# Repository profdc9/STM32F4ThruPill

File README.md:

This is a Bluepill pinout-compatible devboard for the STM32F405RGT6 LQFP-64 microcontroller.
It uses all through-hole parts except for the microcontroller
and is intended to be an alternative that is easier to assemble
should the Bluepill not be available or suitable.  
This material is copyrighted by Daniel Marks (KW4TI) and licensed under
the Creative Commons License CC-BY-SA 4.0.  Software is copyrighted using the zlib
open-source license.

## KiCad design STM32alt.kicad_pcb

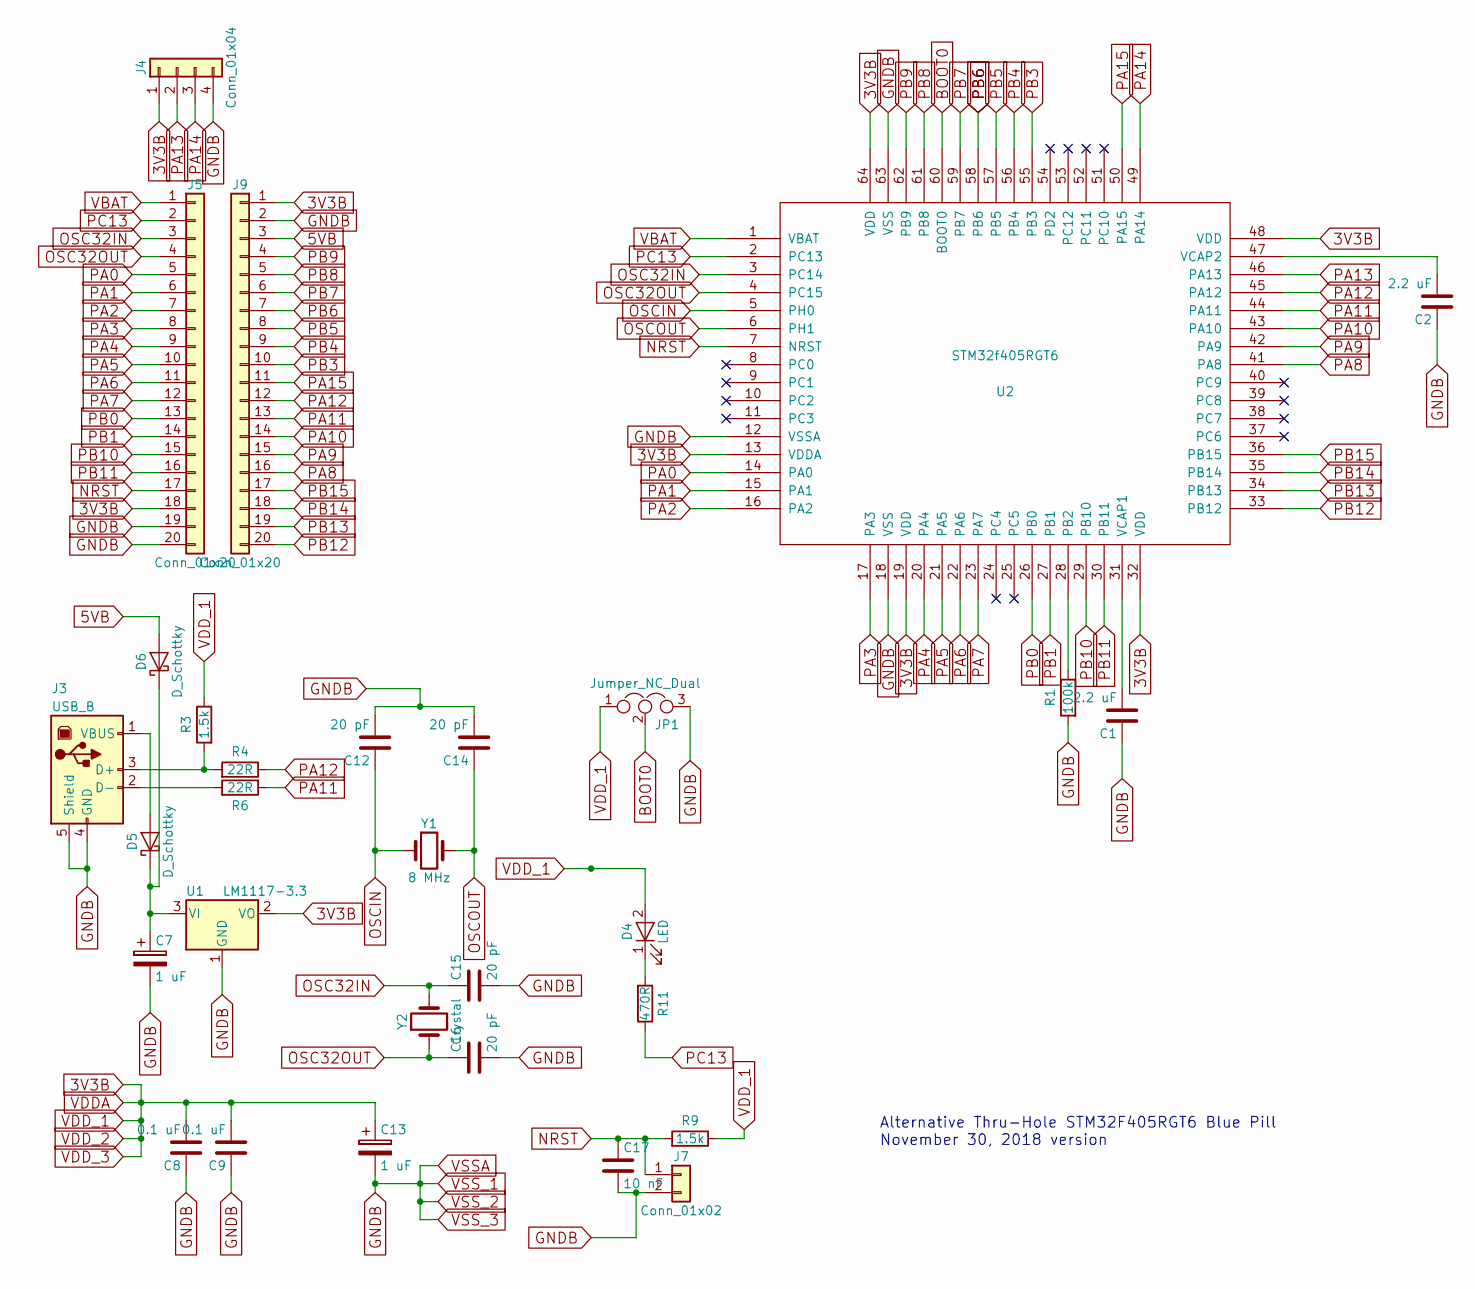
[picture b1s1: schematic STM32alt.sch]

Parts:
C1, C2: 2.2 uF; C_Disc_D5.0mm_W2.5mm_P2.50mm
C7, C13: 1 uF; CP_Radial_D5.0mm_P2.50mm
C8, C9: 0.1 uF; C_Disc_D5.0mm_W2.5mm_P2.50mm
C12, C14, C15, C16: 20 pF; C_Disc_D5.0mm_W2.5mm_P2.50mm
C17: 10 nF; C_Disc_D5.0mm_W2.5mm_P2.50mm
D4: LED; LED_D3.0mm
D5, D6: D_Schottky; D_DO-41_SOD81_P7.62mm_Horizontal
J3: USB_B
J4: Conn_01x04; Pin_Header_Straight_1x04_Pitch2.54mm
J5, J9: Conn_01x20; Pin_Header_Straight_1x20_Pitch2.54mm
J7: Conn_01x02; SW_PUSH_6mm
JP1: Jumper_NC_Dual; Pin_Header_Straight_1x03_Pitch2.54mm
R1: 100k; R_Axial_DIN0207_L6.3mm_D2.5mm_P7.62mm_Horizontal
R3, R9: 1.5k; R_Axial_DIN0207_L6.3mm_D2.5mm_P7.62mm_Horizontal
R4, R6: 22R; R_Axial_DIN0207_L6.3mm_D2.5mm_P7.62mm_Horizontal
R11: 470R; R_Axial_DIN0207_L6.3mm_D2.5mm_P7.62mm_Horizontal
U1: LM1117-3.3; TO-220-3_Vertical
U2: STM32f405RGT6; LQFP-64_10x10mm_Pitch0.5mm
Y1: 8 MHz; Crystal_HC49-U_Vertical
Y2: Crystal; Crystal_Round_d2.0mm_Vertical

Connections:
3V3B: C8.2, C9.2, C13.1, D4.2 (A), J4.1, J5.18, J9.1, JP1.1, R3.1, R9.1, U1.2 (VO), U2.13 (VDDA), U2.19 (VDD), U2.32 (VDD), U2.48 (VDD), U2.64 (VDD)
5VB: D6.2 (A), J9.3
BOOT0: JP1.2, U2.60 (BOOT0)
GNDB: C1.1, C2.1, C7.2, C8.1, C9.1, C12.2, C13.2, C14.2, C15.2, C16.2, C17.2, J3.4 (GND), J3.5 (Shield), J4.4, J5.19, J5.20, J7.2, J9.2, JP1.3, R1.2, U1.1 (GND), U2.12 (VSSA), U2.18 (VSS), U2.63 (VSS)
NRST: C17.1, J5.17, J7.1, R9.2, U2.7 (NRST)
unnamed: C1.2, U2.31 (VCAP1)
unnamed: C2.2, U2.47 (VCAP2)
unnamed: C7.1, D5.1 (K), D6.1 (K), U1.3 (VI)
unnamed: D4.1 (K), R11.2
unnamed: D5.2 (A), J3.1 (VBUS)
unnamed: J3.2 (D-), R6.2
unnamed: J3.3 (D+), R3.2, R4.2
unnamed: R1.1, U2.28 (PB2)
OSC32IN: C15.1, J5.3, U2.3 (PC14), Y2.2
OSC32OUT: C16.1, J5.4, U2.4 (PC15), Y2.1
OSCIN: C12.1, U2.5 (PH0), Y1.1
OSCOUT: C14.1, U2.6 (PH1), Y1.2
PA0: J5.5, U2.14 (PA0)
PA1: J5.6, U2.15 (PA1)
PA2: J5.7, U2.16 (PA2)
PA3: J5.8, U2.17 (PA3)
PA4: J5.9, U2.20 (PA4)
PA5: J5.10, U2.21 (PA5)
PA6: J5.11, U2.22 (PA6)
PA7: J5.12, U2.23 (PA7)
PA8: J9.16, U2.41 (PA8)
PA9: J9.15, U2.42 (PA9)
PA10: J9.14, U2.43 (PA10)
PA11: J9.13, R6.1, U2.44 (PA11)
PA12: J9.12, R4.1, U2.45 (PA12)
PA13: J4.2, U2.46 (PA13)
PA14: J4.3, U2.49 (PA14)
PA15: J9.11, U2.50 (PA15)
PB0: J5.13, U2.26 (PB0)
PB1: J5.14, U2.27 (PB1)
PB3: J9.10, U2.55 (PB3)
PB4: J9.9, U2.56 (PB4)
PB5: J9.8, U2.57 (PB5)
PB6: J9.7, U2.58 (PB6)
PB7: J9.6, U2.59 (PB7)
PB8: J9.5, U2.61 (PB8)
PB9: J9.4, U2.62 (PB9)
PB10: J5.15, U2.29 (PB10)
PB11: J5.16, U2.30 (PB11)
PB12: J9.20, U2.33 (PB12)
PB13: J9.19, U2.34 (PB13)
PB14: J9.18, U2.35 (PB14)
PB15: J9.17, U2.36 (PB15)
PC13: J5.2, R11.1, U2.2 (PC13)
VBAT: J5.1, U2.1 (VBAT)

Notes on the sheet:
Alternative Thru-Hole STM32F405RGT6 Blue Pill November 30, 2018 version

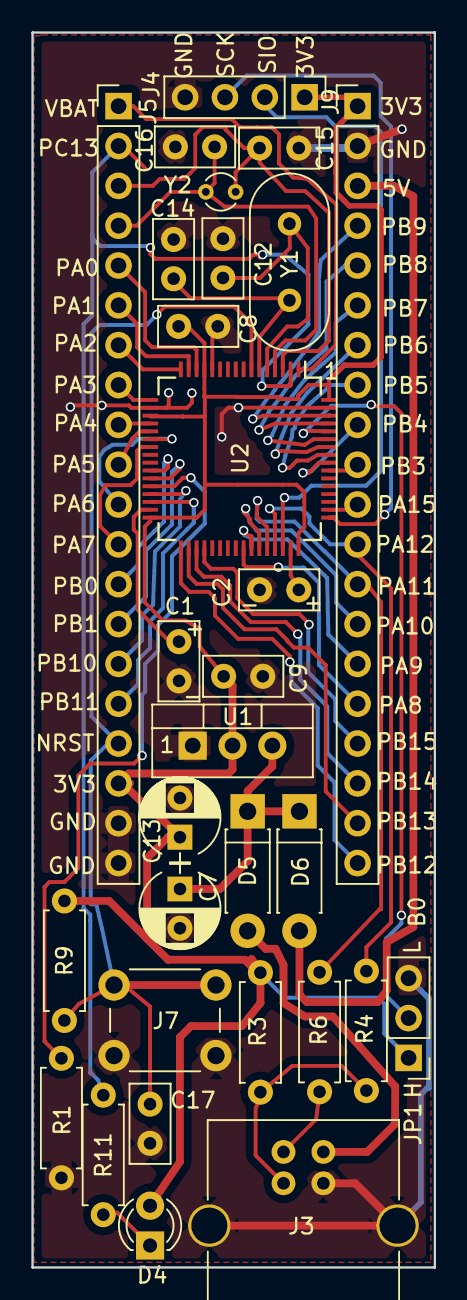
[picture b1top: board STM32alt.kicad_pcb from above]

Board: 2 copper layers, 25.7 x 78.7 mm, 30 parts (0 on the bottom side), 50 nets.

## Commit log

2018-12-01 First Version of Board
2018-12-07 Added pull down on BOOT1
